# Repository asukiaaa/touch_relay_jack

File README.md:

# touch_relay_jack

Control a audio jack with using relay referencing touch sensor value.

# Pin assign

Pro Micro Pin | Role
--------- | ----
D4 | Relay
D8 | Touch signal in
D9 | Touch signal out

# Components

- [Relay](http://akizukidenshi.com/catalog/g/gP-01346/)
- [Mosfet](http://akizukidenshi.com/catalog/g/gI-04256/)
- [Diode](http://akizukidenshi.com/catalog/g/gI-06467/)
- [Resistor 1k](http://akizukidenshi.com/catalog/g/gR-06102/)
- Resistor for touch sensor: [220k](http://akizukidenshi.com/catalog/g/gR-06224/) or [1M](http://akizukidenshi.com/catalog/g/gR-06105/)
- [3.5mm audio jack](http://akizukidenshi.com/catalog/g/gC-02460/)
- [LED Green](http://akizukidenshi.com/catalog/g/gI-06417/)
- Pin Socket
- Pro Micro

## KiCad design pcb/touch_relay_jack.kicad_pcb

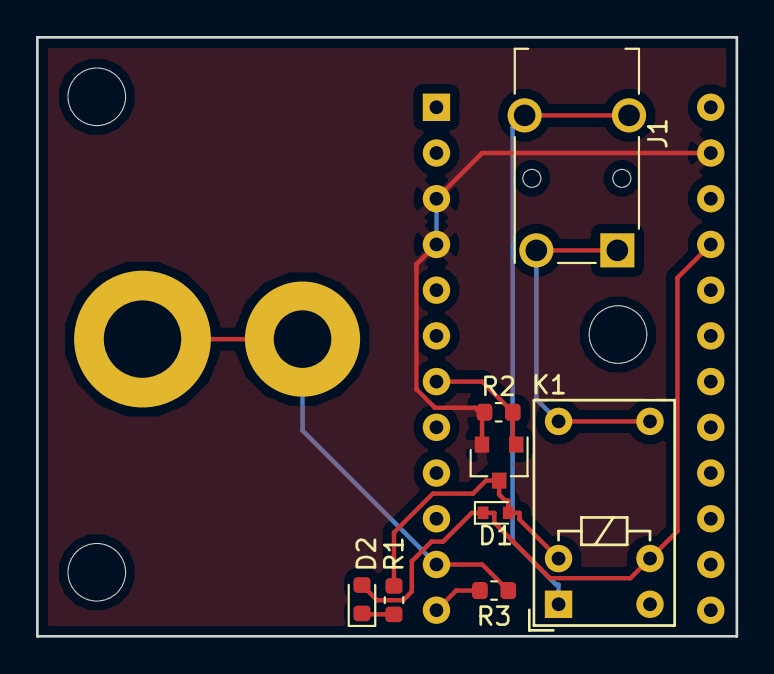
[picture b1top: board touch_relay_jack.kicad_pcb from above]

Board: 2 copper layers, 38.9 x 33.3 mm, 14 parts (0 on the bottom side), 9 nets.

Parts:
A1: Pro_Micro
D1: D_Shockley; D_SOD-523
D2: LED; LED_0603_1608Metric
H1: M4Hole; MountingHole_4.3mm_M4_ISO7380_Pad
H2: M3Hole; MountingHole_3.2mm_M3_Pad
J1: AudioJack3_Ground; Jack_3.5mm_Switronic_ST-005-G_horizontal
K1: Y14x-1C-xxDS; Relay_SPDT_HsinDa_Y14
Q1: Q_NMOS_GSD; SOT-23
R1, R2: 1K; R_0603_1608Metric
R3: 1M; R_0603_1608Metric
REF1, REF2, REF3: MountingHole_3.2mm_M3

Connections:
+5V: A1.21, D1.1, D2.2, K1.4
GND: A1.3, A1.4, A1.23, Q1.2, R2.1
unnamed: A1.11, H1.1, H2.1, R3.1
unnamed: A1.12, R3.2
unnamed: D1.2, K1.3, Q1.3, R1.1
unnamed: D2.1, R1.2
unnamed: J1.R, J1.S, K1.5, K1.6
unnamed: J1.T, K1.1
Relay: A1.7, Q1.1, R2.2

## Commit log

2018-10-26 Create gerber files to order pcb
2018-10-26 Add avr program
2018-10-26 Add register info for touch sensor
2018-10-27 Add case and cover
2018-10-28 Adjust hole position and usb cover style
2018-10-28 Add missing support for hook
2018-10-28 Add image for readme
